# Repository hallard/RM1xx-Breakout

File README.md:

Laird LoRa/Bluetooth Low Energy Module breakout for RM1xx modules
=================================================================

These breakout are used to hold Lairdtech Lora/BLE [module][1] RM186 (868MHz) or RM191 (915MHz). There are 2 versions, one minimal to place on veroboard kind and one other the be placed on breadboard
They contains the following features

- Full version
  - I2C Pullups placement
  - CR2540 or LIR2450 battery holder
  - Resistor divider to measure battery voltage using analog pin
  - On board 3V3 regulator (so Lipo can be used) 
  - JST2 Lipo connector
  - FTDI connector
  - Prog/Debug connector footprint
  - Breadboard friendly

- Minimal version
  - I2C Pullups placement
  - Veroboard friendly

Version 1.1 fix the MCP1303 Regulator that was reversed

Boards have been ordered at PCBs.io and have been tested and they are working fine.

Detailed Description
====================

Look at the schematics for more informations.

- Full version 
  - Place R6 and R7 divider only if you need to measure Vbat from Analog SIO04
  - Place R3 and R4 only if you whan to use I2C devices

- Minimal version 
  - Place R1 and R2 only if you whan to use I2C devices

### Schematic 

**Full version**
Click to enlarge 

**Minimal version**
Click to enlarge 

### Boards (Full Version)

**Top**    

**Bottom**    

You can order the PCB of this board at [PCBs.io][3] if you do so, PCBs.io give me little discount that allow me to buy some new created boards.

### Boards (Minimal Version)

**Top**    

**Bottom**    

You can order the PCB of this minimal breakout board at [PCBs.io][4] if you do so, PCBs.io give me little discount that allow me to buy some new created boards.

### Assembled boards

###License

You can do whatever you like with this design.

###Misc
See news and other projects on my [blog][2] 

[1]: http://www.lairdtech.com/products/rm1xx-lora-modules
[2]: https://hallard.me
[3]: https://PCBs.io/share/rY657 
[4]: https://PCBs.io/share/49GYW

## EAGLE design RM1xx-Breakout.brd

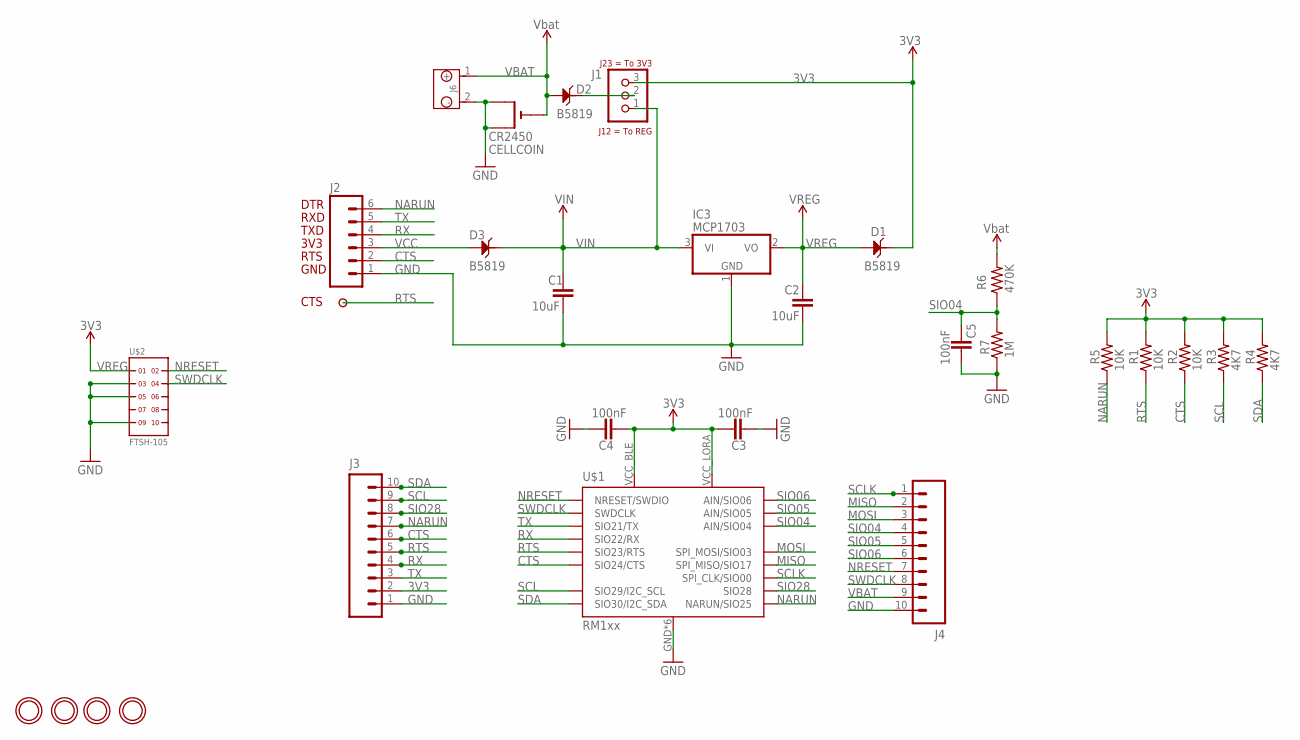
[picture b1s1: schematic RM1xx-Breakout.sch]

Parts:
C1, C2: 10uF; 0805-CAP
C3, C4, C5: 100nF; 0805-CAP
CELLCOIN: CR2450; CR2450-SMD
D1, D2, D3: B5819; SOD123-2.7X1.6
IC3: MCP1703; SOT23
J1: JUMPER_1X30805; JP3_0805
J2: M06SIP_LOCK; 1X06-SIP_LOCK
J3, J4: M10LOCK; 1X10_LOCK
J6: Lipo Battery; 2P-2.0-90D
P1: PADNORMAL; PAD
R1, R2, R5: 10K; 0805-RES
R3, R4: 4K7; 0805-RES
R6: 470K; 0805-RES
R7: 1M; 0805-RES
U$1: RM1xx; RM1XX
U$2: FTSH-105; FTSH-105-01-XXX-DV-K
U$3, U$6, U$7, U$8: MOUNTINGHOLE2.5; MOUNTINGHOLE_2.5_PLATED

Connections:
3V3: C3.1, C4.2, D1.2, J1.3, J3.2, R1.2, R2.2, R3.2, R4.2, R5.2, U$1.VCC_BLE, U$1.VCC_LORA
CTS: J2.2, J3.6, R2.1, U$1.SIO24 (SIO24/CTS)
GND: C1.2, C2.2, C3.2, C4.1, C5.1, CELLCOIN.+$1 (+), CELLCOIN.+$2 (+1), IC3.1 (GND), J2.1, J3.1, J4.10, J6.2 (-), R7.1, U$1.GND, U$1.GND1 (GND), U$1.GND2 (GND), U$1.GND3 (GND), U$1.GND4 (GND), U$1.GND5 (GND), U$2.3, U$2.5, U$2.9
MISO: J4.2, U$1.SIO17 (SPI_MISO/SIO17)
MOSI: J4.3, U$1.SIO03 (SPI_MOSI/SIO03)
unnamed: D2.2, J1.2
NARUN: J2.6, J3.7, R5.1, U$1.SIO25 (NARUN/SIO25)
NRESET: J4.7, U$1.RESET (NRESET/SWDIO), U$2.2
RTS: J3.5, P1.1, R1.1, U$1.SIO23 (SIO23/RTS)
RX: J2.4, J3.4, U$1.SIO22 (SIO22/RX)
SCL: J3.9, R3.1, U$1.SIO29 (SIO29/I2C_SCL)
SCLK: J4.1, U$1.SIO00 (SPI_CLK/SIO00)
SDA: J3.10, R4.1, U$1.SIO30 (SIO30/I2C_SDA)
SIO04: C5.2, J4.4, R6.1, R7.2, U$1.SIO04 (AIN/SIO04)
SIO05: J4.5, U$1.SIO05 (AIN/SIO05)
SIO06: J4.6, U$1.SIO06 (AIN/SIO06)
SIO28: J3.8, U$1.SIO28
SWDCLK: J4.8, U$1.SWDCLK, U$2.4
TX: J2.5, J3.3, U$1.SIO21 (SIO21/TX)
VBAT: CELLCOIN.-, D2.1, J4.9, J6.1 (+), R6.2
VCC: D3.1, J2.3
VIN: C1.1, D3.2, IC3.3 (VI), J1.1
VREG: C2.1, D1.1, IC3.2 (VO), U$2.1

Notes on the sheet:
DTR
RXD
TXD
3V3
RTS
GND
CTS

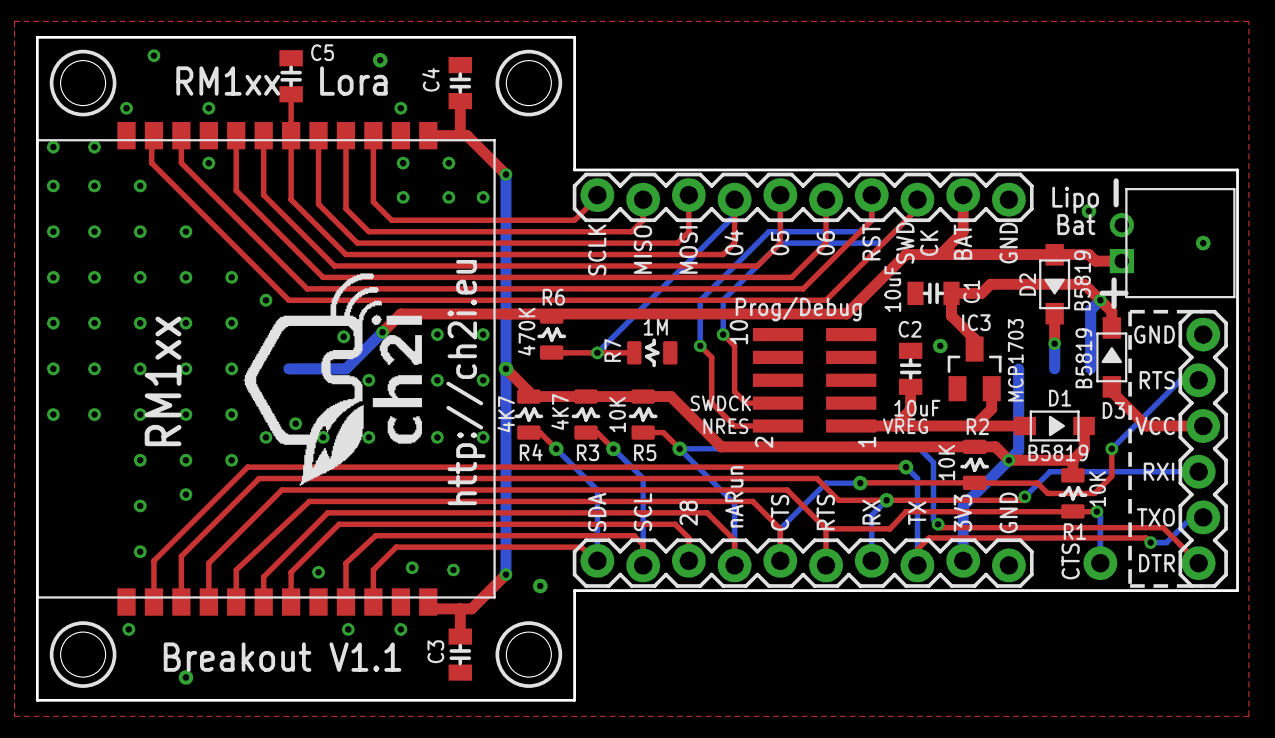
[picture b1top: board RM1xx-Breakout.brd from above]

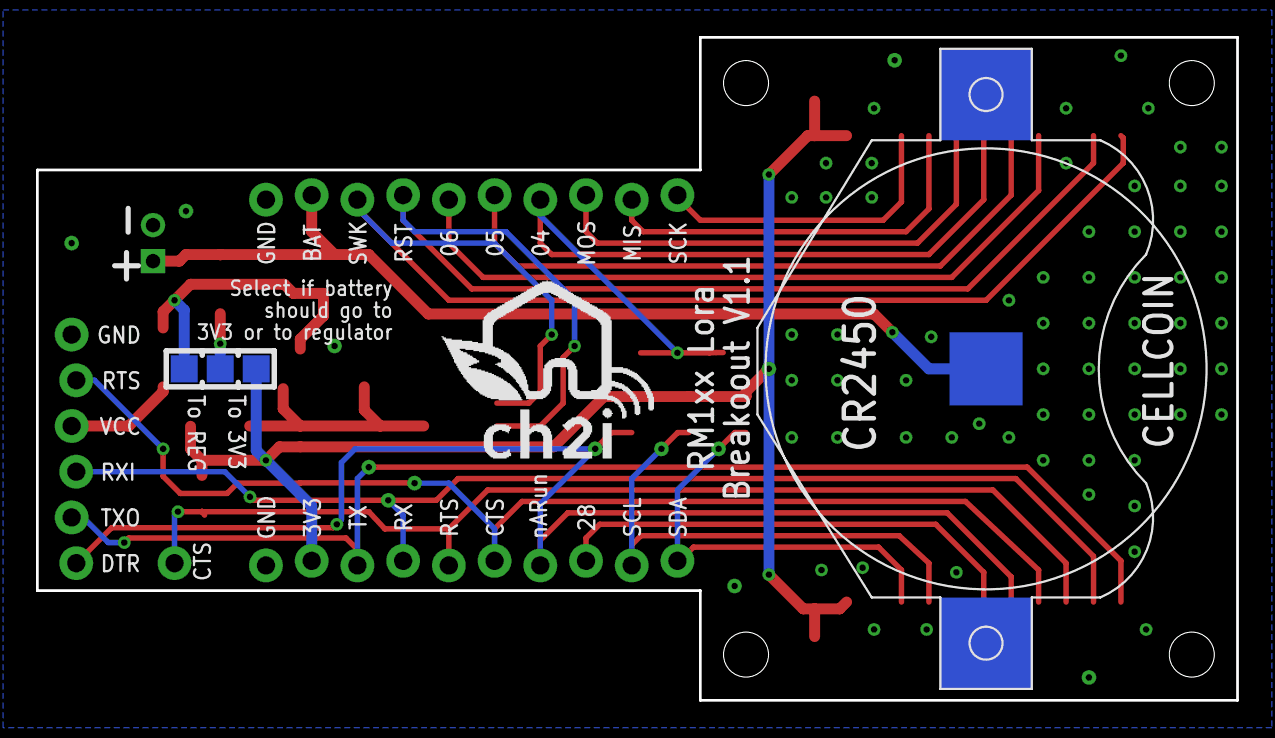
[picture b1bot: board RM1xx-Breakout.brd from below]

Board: 2 copper layers, 66.7 x 36.8 mm, 31 parts (3 on the bottom side), 23 nets.

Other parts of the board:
U$4, U$5: LOGO_CH2I_110MM

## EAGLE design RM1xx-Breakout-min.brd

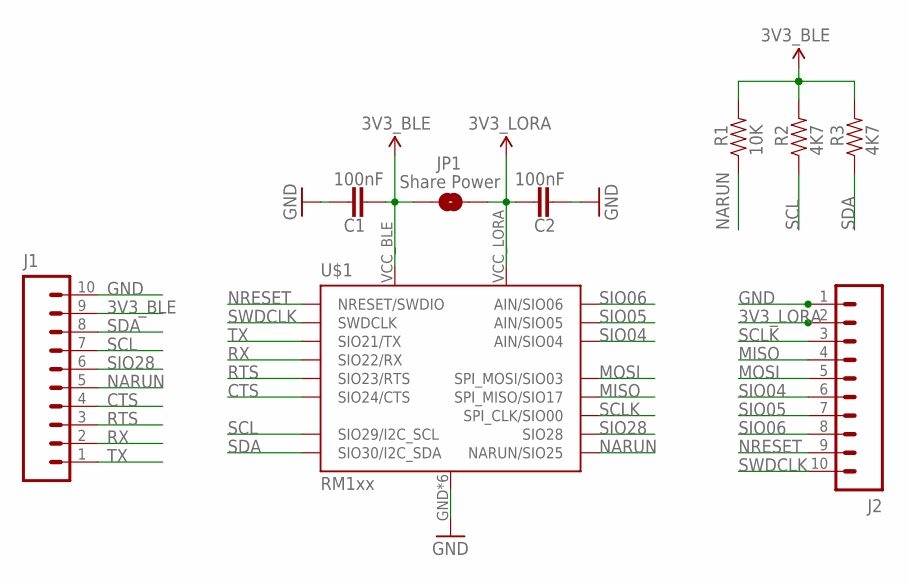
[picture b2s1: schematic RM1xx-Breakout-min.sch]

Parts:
C1, C2: 100nF; 0805-CAP
J1, J2: M10LOCK; 1X10_LOCK
JP1: Share Power; PAD-JUMPER-2-NO_YES_SILK
R1: 10K; 0805-RES
R2, R3: 4K7; 0805-RES
U$1: RM1xx; RM1XX

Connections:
3V3_BLE: C1.2, J1.9, JP1.1, R1.2, R2.2, R3.2, U$1.VCC_BLE
3V3_LORA: C2.1, J2.2, JP1.2, U$1.VCC_LORA
CTS: J1.4, U$1.SIO24 (SIO24/CTS)
GND: C1.1, C2.2, J1.10, J2.1, U$1.GND, U$1.GND1 (GND), U$1.GND2 (GND), U$1.GND3 (GND), U$1.GND4 (GND), U$1.GND5 (GND)
MISO: J2.4, U$1.SIO17 (SPI_MISO/SIO17)
MOSI: J2.5, U$1.SIO03 (SPI_MOSI/SIO03)
NARUN: J1.5, R1.1, U$1.SIO25 (NARUN/SIO25)
NRESET: J2.9, U$1.RESET (NRESET/SWDIO)
RTS: J1.3, U$1.SIO23 (SIO23/RTS)
RX: J1.2, U$1.SIO22 (SIO22/RX)
SCL: J1.7, R2.1, U$1.SIO29 (SIO29/I2C_SCL)
SCLK: J2.3, U$1.SIO00 (SPI_CLK/SIO00)
SDA: J1.8, R3.1, U$1.SIO30 (SIO30/I2C_SDA)
SIO04: J2.6, U$1.SIO04 (AIN/SIO04)
SIO05: J2.7, U$1.SIO05 (AIN/SIO05)
SIO06: J2.8, U$1.SIO06 (AIN/SIO06)
SIO28: J1.6, U$1.SIO28
SWDCLK: J2.10, U$1.SWDCLK
TX: J1.1, U$1.SIO21 (SIO21/TX)

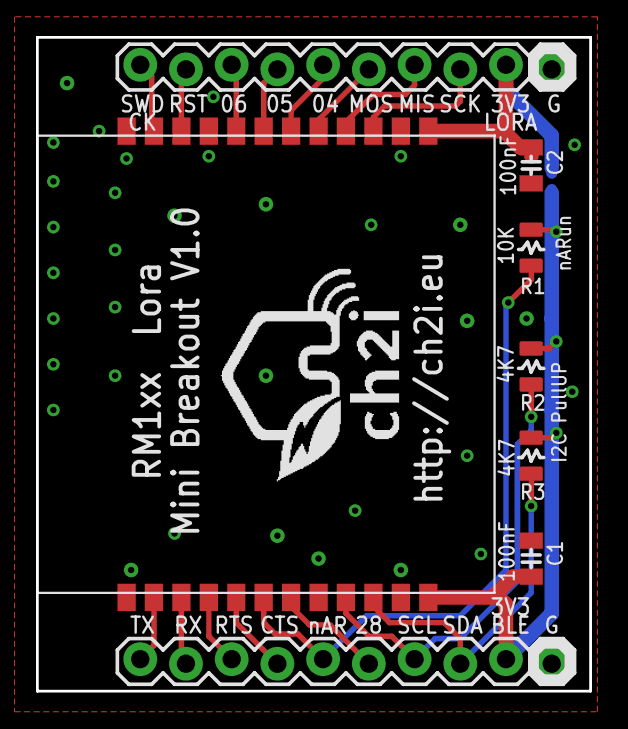
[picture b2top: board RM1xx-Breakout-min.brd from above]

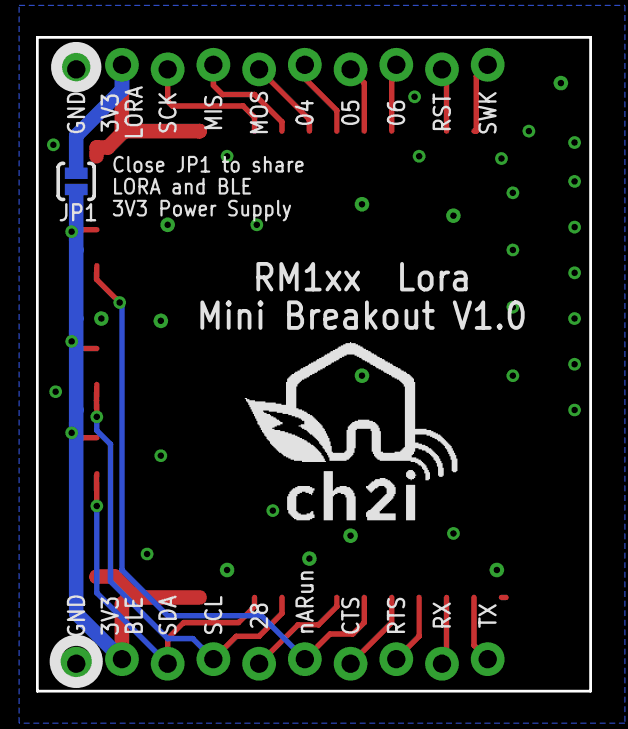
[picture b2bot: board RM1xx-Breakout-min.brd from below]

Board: 2 copper layers, 30.7 x 36.3 mm, 11 parts (2 on the bottom side), 19 nets.

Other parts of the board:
U$2, U$4: LOGO_CH2I_110MM

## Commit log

2016-07-17 Creation
2016-07-17 Type
2016-07-17 Changed PCBs.io link
2016-07-17 removed copper on mounting holes
2016-07-17 version 1.0b
    Removed copper from mounting holes
    Added ground via under RM1xx module
2016-07-17 Version 1.0a
2016-10-22 Added Minimal Breakout
2017-06-08 Version 1.1

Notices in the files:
parts and their libraries:
SparkFun-Connectors: Licensing: Creative Commons ShareAlike 4.0 International - https://creativecommons.org/licenses/by-sa/4.0
microbuilder: This work is placed in the public domain, and may be freely used for commercial and non-commercial work with the following conditions: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
